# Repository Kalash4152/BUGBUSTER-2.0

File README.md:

🔌 Hardware Hackathon Experience – BugBusteer 2.0! ⚡💡
Recently participated in BugBusteer 2.0, a hardware hackathon that pushed electronics skills to the limit! This 6-hour challenge tested technical expertise, circuit design proficiency, and problem-solving abilities under extreme time constraints. 🚀⚙️

🔥 Hackathon Rounds:
✅ Round 1: A brain-teasing electronics quiz 🧠 to assess fundamental concepts.
✅ Round 2: A high-stakes circuit simulation & PCB design challenge using Proteus & Eagle. 🖥️🔧

💡 The Challenge:
The task was to design a PCB for an automotive application, integrating multiple electronic components into a functional circuit. The real challenge? Encountering new components and learning their functionality on the fly! 😵‍💫 This involved:
🔍 Researching component datasheets 📜
🔗 Debugging circuit connections 🤯
🛠️ Optimizing PCB design for efficiency & functionality 🎯

Though the final design wasn’t completed in time, the experience provided invaluable hands-on learning in circuit design, PCB layout, and real-world problem-solving. This was just the beginning—bigger challenges ahead! 🔥🚀

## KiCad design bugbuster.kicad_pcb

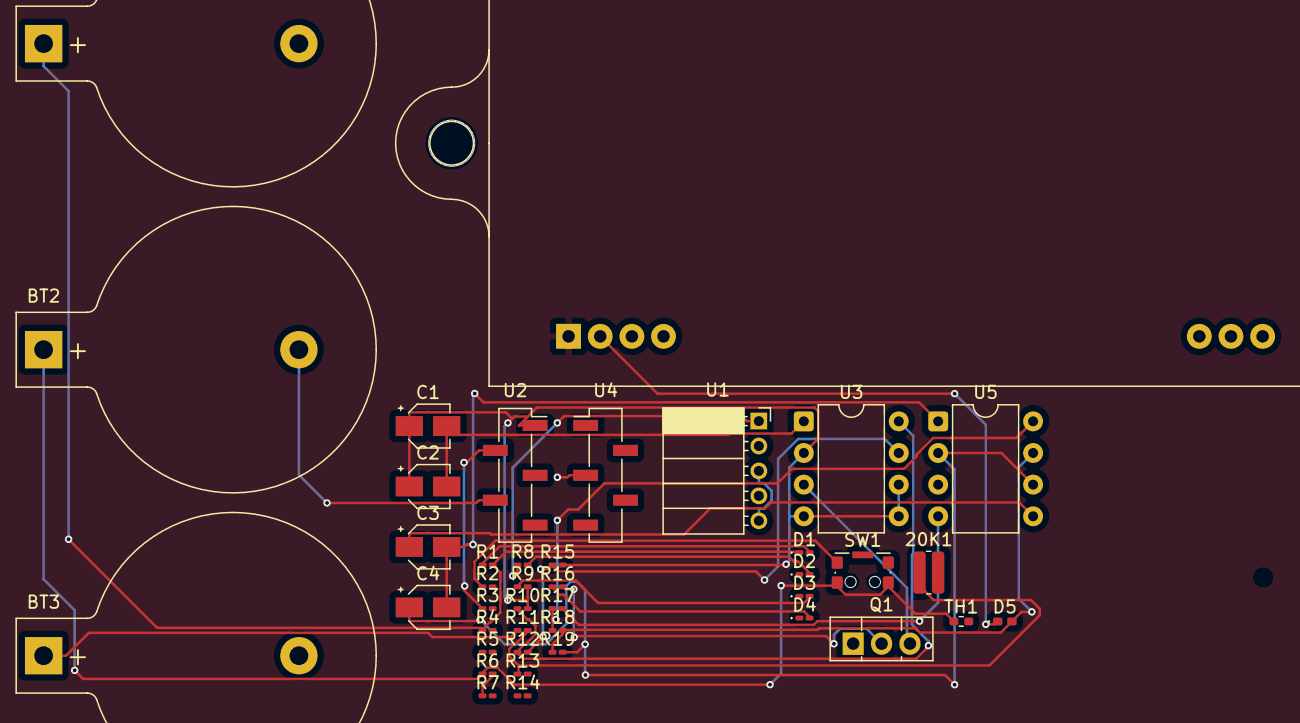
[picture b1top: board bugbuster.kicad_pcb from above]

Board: 2 copper layers, 41 parts (0 on the bottom side), 28 nets.

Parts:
20K1: Thermistor_NTC; R_0612_1632Metric
BT1: 12v; BatteryHolder_Keystone_103_1x20mm
BT2: 12V; BatteryHolder_Keystone_103_1x20mm
BT3: Battery; BatteryHolder_Keystone_103_1x20mm
BZ1: Buzzer; Reverb_BTDR-1H
C1, C2: 0.01UF; CP_Elec_3x5.3
C3, C4: 0.01uf; CP_Elec_3x5.3
D1, D4: RED_LED; LED_0201_0603Metric_Pad0.64x0.40mm_HandSolder
D2: YELLOW_LED; LED_0201_0603Metric_Pad0.64x0.40mm_HandSolder
D3: LED_GREEN; LED_0201_0603Metric_Pad0.64x0.40mm_HandSolder
D5: 1N4007; D_0402_1005Metric_Pad0.77x0.64mm_HandSolder
Q1: BC457; TO-126-3_Vertical
R1, R8, R16: 220; R_0201_0603Metric_Pad0.64x0.40mm_HandSolder
R2, R3, R4, R5: 10k; R_0201_0603Metric_Pad0.64x0.40mm_HandSolder
R6: 1OK; R_0201_0603Metric_Pad0.64x0.40mm_HandSolder
R7, R9, R11, R12, R13, R14: 10K; R_0201_0603Metric_Pad0.64x0.40mm_HandSolder
R10: 4.7K; R_0201_0603Metric_Pad0.64x0.40mm_HandSolder
R15: 50K; R_0201_0603Metric_Pad0.64x0.40mm_HandSolder
R17: 4.7k; R_0201_0603Metric_Pad0.64x0.40mm_HandSolder
R18: 1k; R_0201_0603Metric_Pad0.64x0.40mm_HandSolder
R19: 50k; R_0201_0603Metric_Pad0.64x0.40mm_HandSolder
SW1: CK_KMS2xxGP; SW_SPST_CK_KMS2xxGP
TH1: Thermistor_NTC; R_0402_1005Metric_Pad0.72x0.64mm_HandSolder
U1: LM358; PinSocket_1x05_P2.00mm_Horizontal
U2: LM358; PinSocket_1x05_P2.00mm_Vertical_SMD_Pin1Right
U3, U5: NE555P; DIP-8_W7.62mm
U4: LM741; PinSocket_1x05_P2.00mm_Vertical_SMD_Pin1Left

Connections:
12V: 20K1.1, R11.2, R13.1
+12V: 20K1.2, BT1.2 (-), BT3.2 (-), D2.1 (K), D3.1 (K), D4.1 (K), Q1.1 (E), R2.2, R3.2, R4.2, R5.1, R5.2, R7.2, R13.2, R14.1, R14.2, TH1.2, U1.2 (-), U1.4 (V-), U2.3 (+), U4.2 (-), U4.4 (V-), U5.3 (Q)
unnamed: BT1.1 (+), D1.1 (K), R1.2, R4.1
unnamed: BT2.1 (+), R6.1, SW1.2, TH1.1
unnamed: BT2.2 (-), U2.4 (V-)
unnamed: BT3.1 (+), R11.1
unnamed: BZ1.2 (-), D5.1 (K)
unnamed: D1.2 (A), R1.1
unnamed: D2.2 (A), R8.2
unnamed: D3.2 (A), R9.1
unnamed: D4.2 (A), R16.1
unnamed: D5.2 (A), R18.2, R19.1, U5.7 (DIS)
unnamed: Q1.3 (B), U3.3 (Q)
unnamed: Q1.2 (C), R16.2
unnamed: R2.1, SW1.1
unnamed: R6.2, R7.1
unnamed: R8.1, U1.1
unnamed: U1.3 (+), U1.5 (+)
unnamed: R3.1, U2.2 (-)
unnamed: C1.1, C2.1, R9.2, R10.2, R15.2, U2.1, U3.2 (TR), U3.4 (R), U3.5 (CV), U3.6 (THR)
unnamed: R12.2, R15.1, U3.7 (DIS)
unnamed: C1.2, C2.2, U3.1 (GND)
unnamed: R10.1, R12.1, U3.8 (VCC)
unnamed: C3.1, U5.5 (CV)
unnamed: C3.2, C4.2, U5.1 (GND)
unnamed: R17.2, U5.4 (R)
unnamed: C4.1, R19.2, U5.2 (TR), U5.6 (THR)
unnamed: R17.1, R18.1, U5.8 (VCC)

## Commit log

2025-03-21 Add files via upload
    BugBusteer 2.0 – Hardware Hackathon Experience ⚡💡
    I recently participated in BugBusteer 2.0, a hardware hackathon organized by SPIT, alongside my teammates Varad Bhandari and Heet Bharadwa. This 6-hour challenge put our electronics and problem-solvi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
    🔥 Hackathon Breakdown:
    ✅ Round 1: Electronics fundamentals quiz 🧠
    ✅ Round 2: Circuit simulation & PCB design challenge using Proteus & Eagle 🖥️🔧
    💡 The Challenge:
2025-03-22 experience.md
